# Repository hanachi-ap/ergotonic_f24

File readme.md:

# Ergotonic F24

Ergotonic F24 comes with a unique adjustable centerpiece making this keyboard split or monoblock on demand.
The Ergotonic F24 extends 30 mm horizontally and allows an adjustment of ±8 degrees with regards of the slant angle. In addition, it can also be completely separated and used as a true split.

- [About Ergotonic F24](https://hanachi-ap.github.io/ergotonic_f24/) (in Japanese)

- [How to build](https://hanachi-ap.github.io/ergotonic_f24/docs/) (in Japanese)

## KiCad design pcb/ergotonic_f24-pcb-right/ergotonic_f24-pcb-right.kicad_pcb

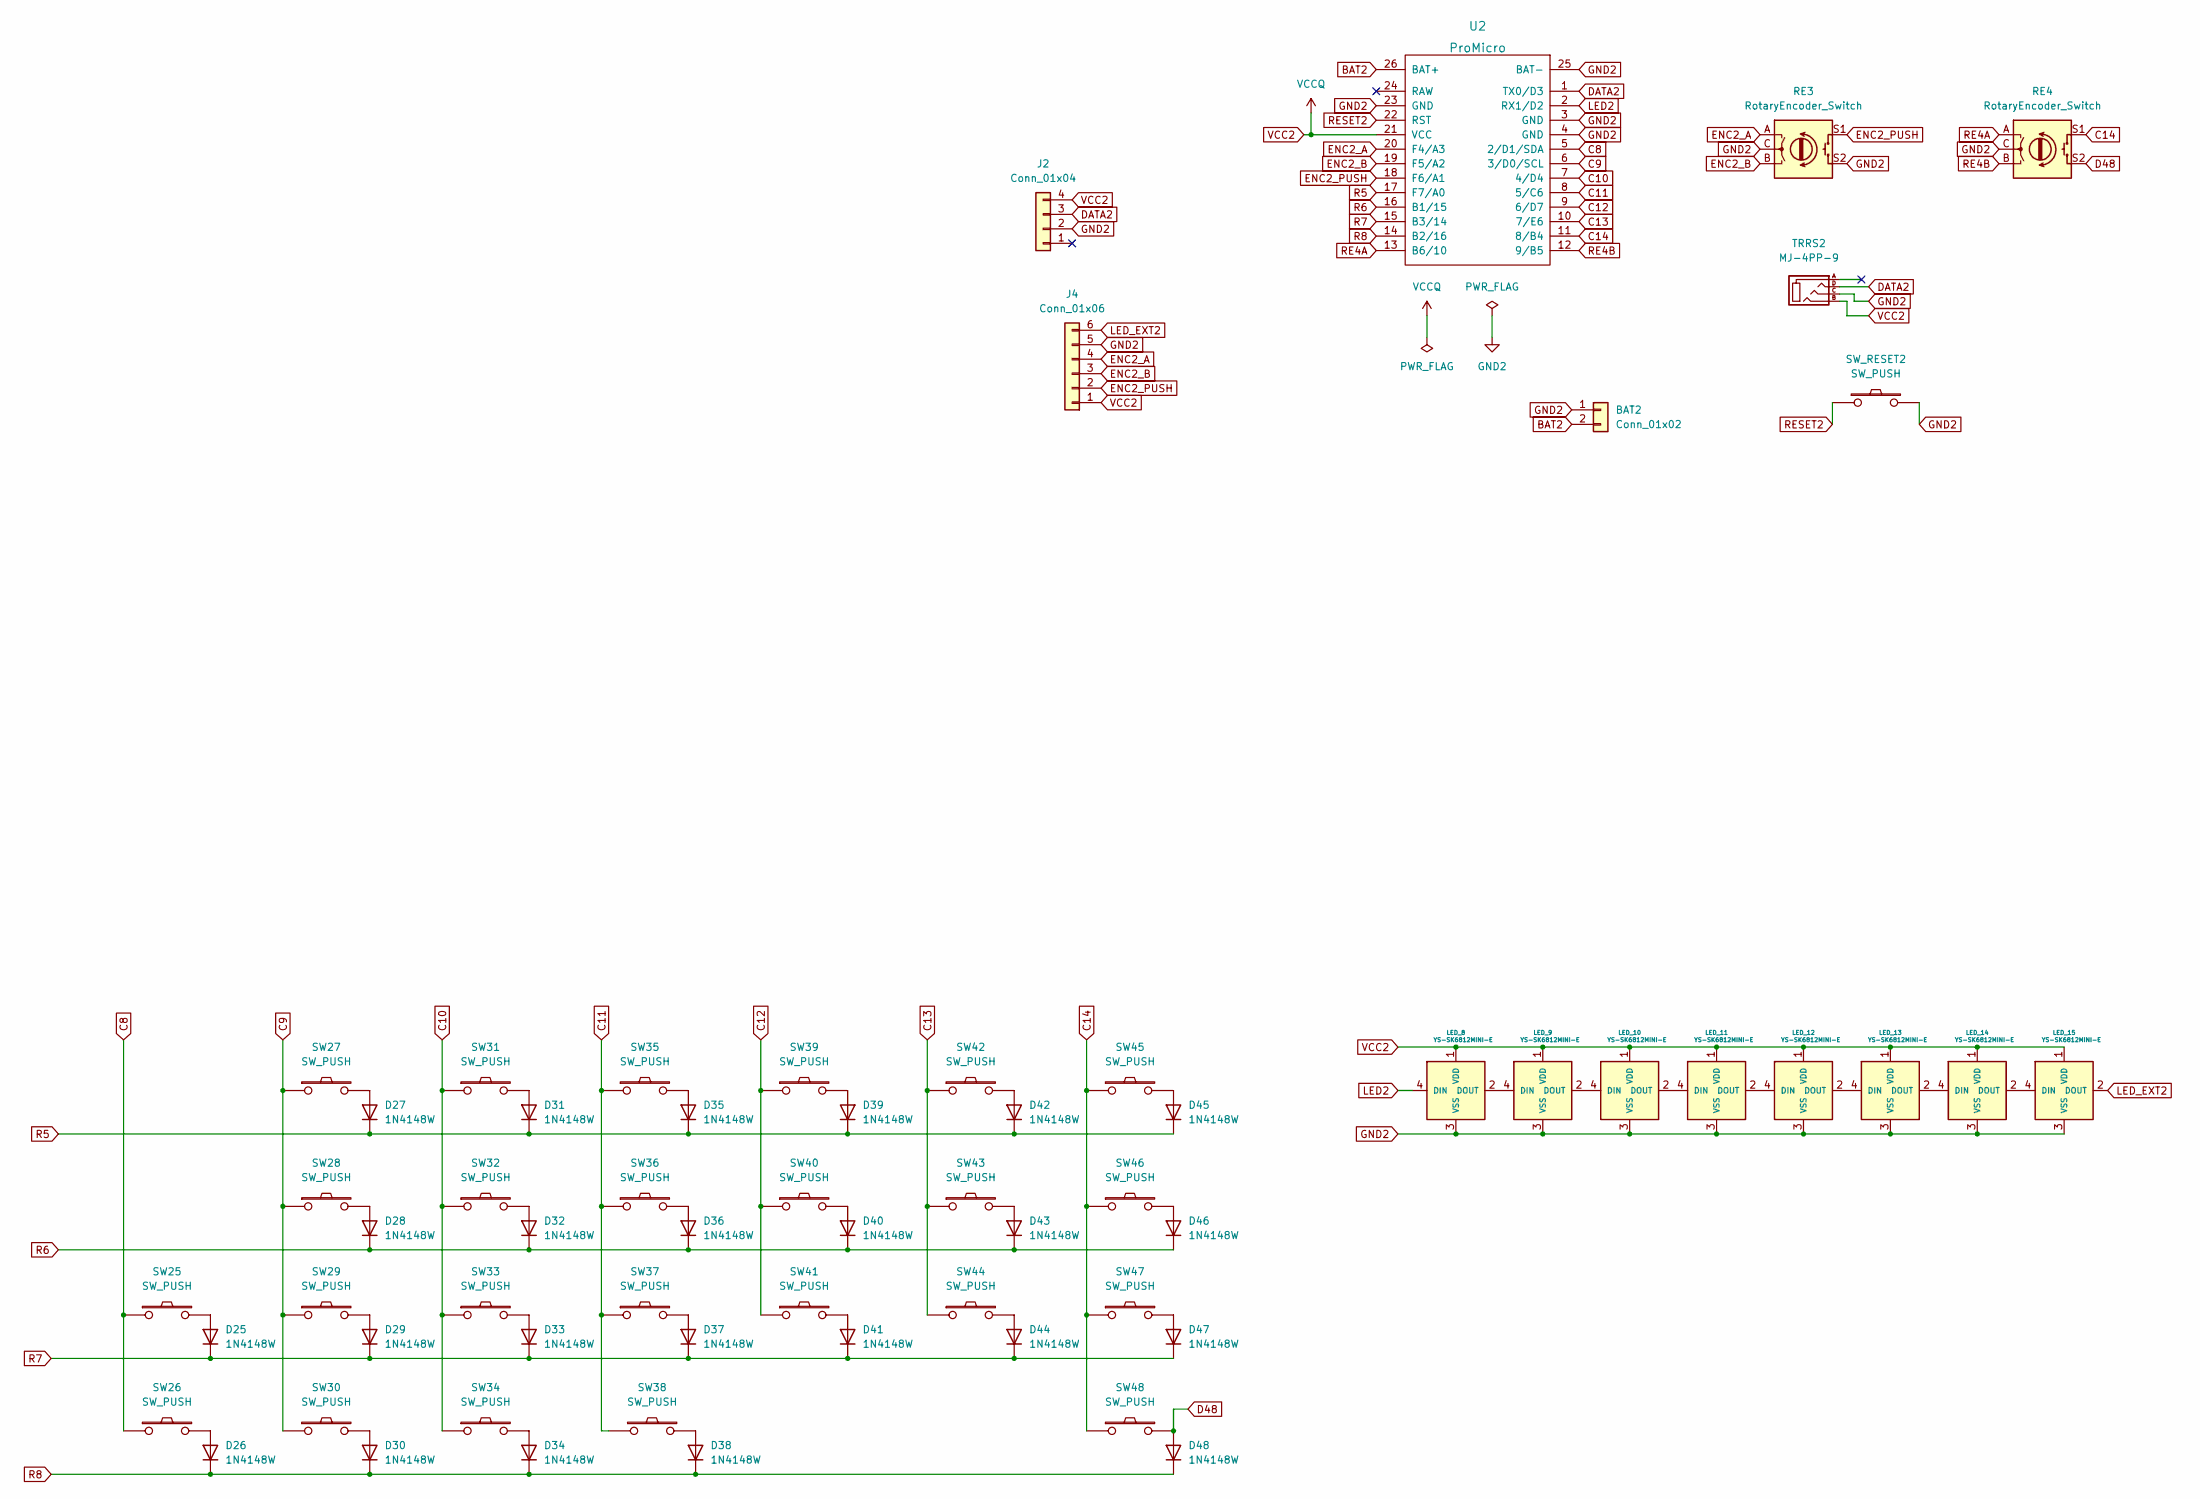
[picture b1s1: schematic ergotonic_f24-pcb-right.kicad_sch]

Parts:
BAT2: Conn_01x02; PinHeader_1x02_P2.54mm_Vertical
D25, D26, D27, D28, D29, D30, D31, D32, D33, D34, D35, D36, D37, D38, D39, D40, D41, D42, D43, D44, D45, D46, D47, D48: 1N4148W; D3_SMD_v2
J2: Conn_01x04; JST_SH_BM03B-SRSS-TB_1x04-1MP_P1.00mm_Vertical
J4: Conn_01x06; JST_SH_BM03B-SRSS-TB_1x06-1MP_P1.00mm_Vertical
LED_8, LED_9, LED_10, LED_11, LED_12, LED_13, LED_14, LED_15: YS-SK6812MINI-E
RE3, RE4: RotaryEncoder_Switch; RotaryEncoder_Alps_EC11E-Switch_Vertical_H20mm_rev2
SW25, SW26, SW27, SW28, SW29, SW30, SW31, SW32, SW33, SW34, SW35, SW36, SW37, SW38, SW39, SW40, SW41, SW42, SW43, SW44, SW45, SW46, SW47, SW48: SW_PUSH; CherryMX_Hotswap
SW_RESET2: SW_PUSH; ResetSW_1side
TRRS2: MJ-4PP-9; MJ-4PP-9_1side
U2: ProMicro

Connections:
BAT2: BAT2.2, U2.26 (BAT+)
C8: SW25.1, SW26.1, U2.5 (2/D1/SDA)
C9: SW27.1, SW28.1, SW29.1, SW30.1, U2.6 (3/D0/SCL)
C10: SW31.1, SW32.1, SW33.1, SW34.1, U2.7 (4/D4)
C11: SW35.1, SW36.1, SW37.1, SW38.1, U2.8 (5/C6)
C12: SW39.1, SW40.1, SW41.1, U2.9 (6/D7)
C13: SW42.1, SW43.1, SW44.1, U2.10 (7/E6)
C14: RE4.S1, SW45.1, SW46.1, SW47.1, SW48.1, U2.11 (8/B4)
D48: D48.2 (A), RE4.S2, SW48.2
DATA2: J2.3, TRRS2.D, U2.1 (TX0/D3)
ENC2_A: J4.4, RE3.A, U2.20 (F4/A3)
ENC2_B: J4.3, RE3.B, U2.19 (F5/A2)
ENC2_PUSH: J4.2, RE3.S1, U2.18 (F6/A1)
GND2: BAT2.1, J2.2, J4.5, LED_8.3 (VSS), LED_9.3 (VSS), LED_10.3 (VSS), LED_11.3 (VSS), LED_12.3 (VSS), LED_13.3 (VSS), LED_14.3 (VSS), LED_15.3 (VSS), RE3.C, RE3.S2, RE4.C, SW_RESET2.2, TRRS2.C, U2.3 (GND), U2.4 (GND), U2.23 (GND), U2.25 (BAT-)
LED2: LED_8.4 (DIN), U2.2 (RX1/D2)
LED_EXT2: J4.6, LED_15.2 (DOUT)
unnamed: D25.2 (A), SW25.2
unnamed: D26.2 (A), SW26.2
unnamed: D27.2 (A), SW27.2
unnamed: D28.2 (A), SW28.2
unnamed: D29.2 (A), SW29.2
unnamed: D30.2 (A), SW30.2
unnamed: D31.2 (A), SW31.2
unnamed: D32.2 (A), SW32.2
unnamed: D33.2 (A), SW33.2
unnamed: D34.2 (A), SW34.2
unnamed: D35.2 (A), SW35.2
unnamed: D36.2 (A), SW36.2
unnamed: D37.2 (A), SW37.2
unnamed: D38.2 (A), SW38.2
unnamed: D39.2 (A), SW39.2
unnamed: D40.2 (A), SW40.2
unnamed: D41.2 (A), SW41.2
unnamed: D42.2 (A), SW42.2
unnamed: D43.2 (A), SW43.2
unnamed: D44.2 (A), SW44.2
unnamed: D45.2 (A), SW45.2
unnamed: D46.2 (A), SW46.2
unnamed: D47.2 (A), SW47.2
unnamed: LED_8.2 (DOUT), LED_9.4 (DIN)
unnamed: LED_10.2 (DOUT), LED_11.4 (DIN)
unnamed: LED_9.2 (DOUT), LED_10.4 (DIN)
unnamed: LED_11.2 (DOUT), LED_12.4 (DIN)
unnamed: LED_12.2 (DOUT), LED_13.4 (DIN)
unnamed: LED_13.2 (DOUT), LED_14.4 (DIN)
unnamed: LED_14.2 (DOUT), LED_15.4 (DIN)
R5: D27.1 (K), D31.1 (K), D35.1 (K), D39.1 (K), D42.1 (K), D45.1 (K), U2.17 (F7/A0)
R6: D28.1 (K), D32.1 (K), D36.1 (K), D40.1 (K), D43.1 (K), D46.1 (K), U2.16 (B1/15)
R7: D25.1 (K), D29.1 (K), D33.1 (K), D37.1 (K), D41.1 (K), D44.1 (K), D47.1 (K), U2.15 (B3/14)
R8: D26.1 (K), D30.1 (K), D34.1 (K), D38.1 (K), D48.1 (K), U2.14 (B2/16)
RE4A: RE4.A, U2.13 (B6/10)
RE4B: RE4.B, U2.12 (9/B5)
RESET2: SW_RESET2.1, U2.22 (RST)
VCC2: J2.4, J4.1, LED_8.1 (VDD), LED_9.1 (VDD), LED_10.1 (VDD), LED_11.1 (VDD), LED_12.1 (VDD), LED_13.1 (VDD), LED_14.1 (VDD), LED_15.1 (VDD), TRRS2.B, U2.21 (VCC)

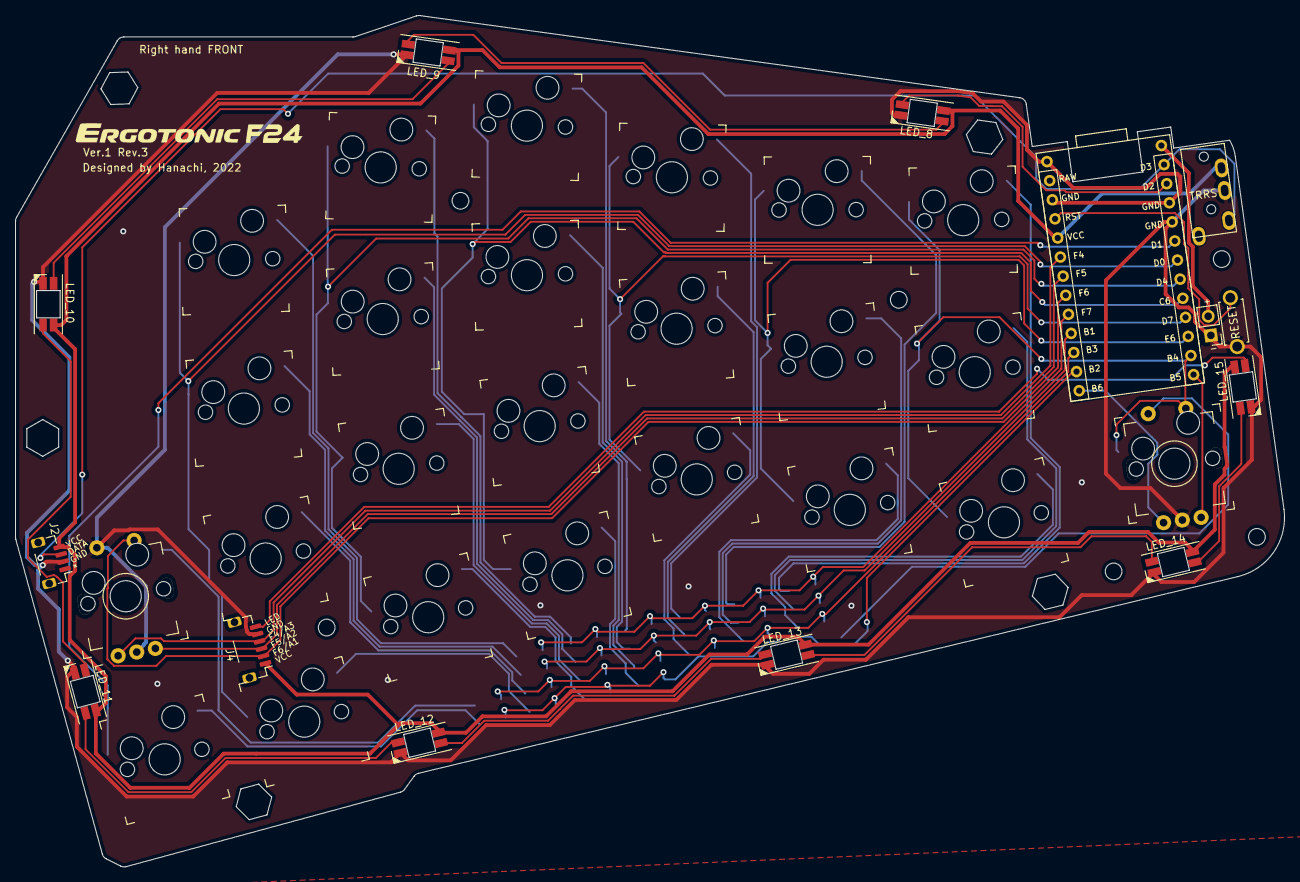
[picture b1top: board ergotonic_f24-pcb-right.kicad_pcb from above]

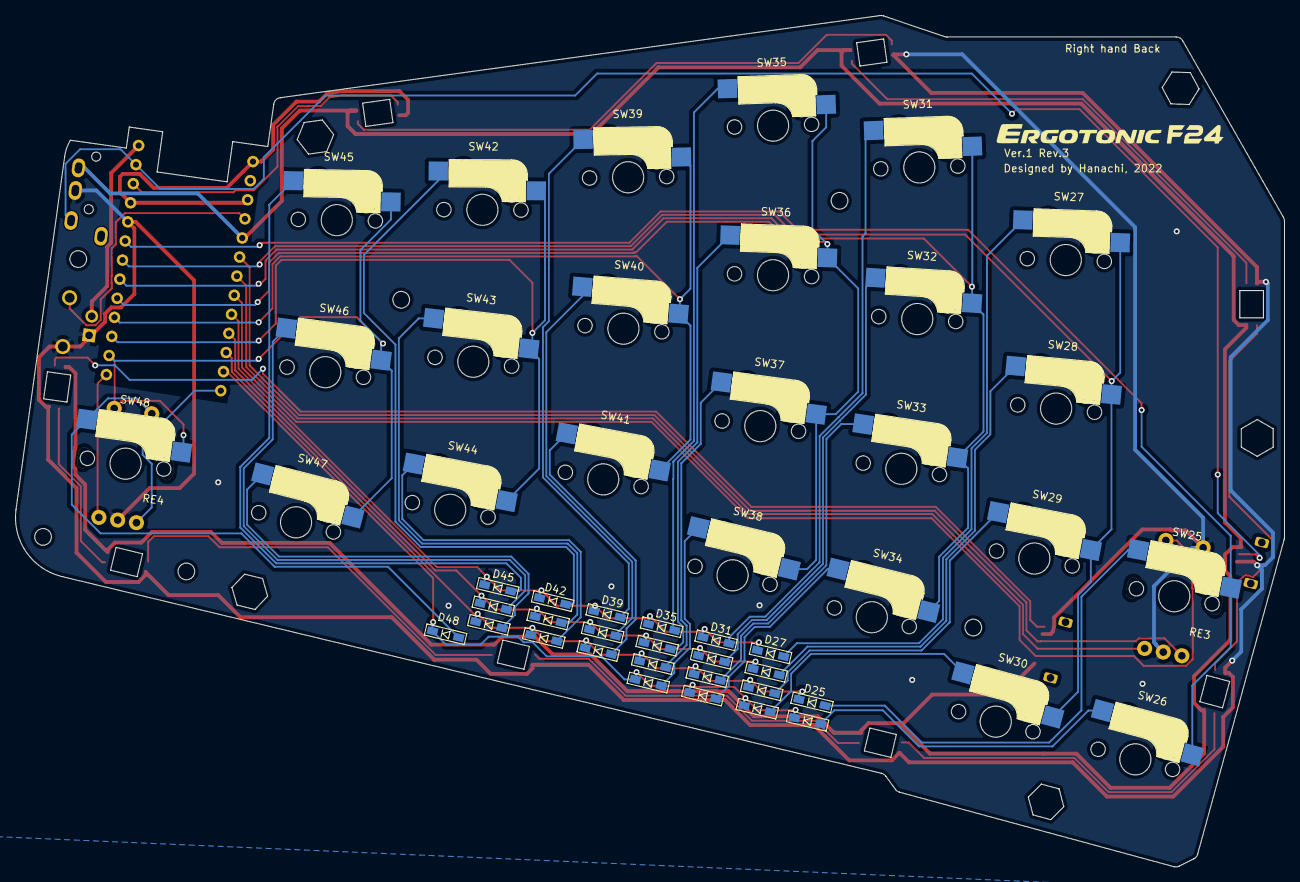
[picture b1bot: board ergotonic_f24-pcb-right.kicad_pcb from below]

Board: 2 copper layers, 167.2 x 112.2 mm, 64 parts (24 on the bottom side), 54 nets.

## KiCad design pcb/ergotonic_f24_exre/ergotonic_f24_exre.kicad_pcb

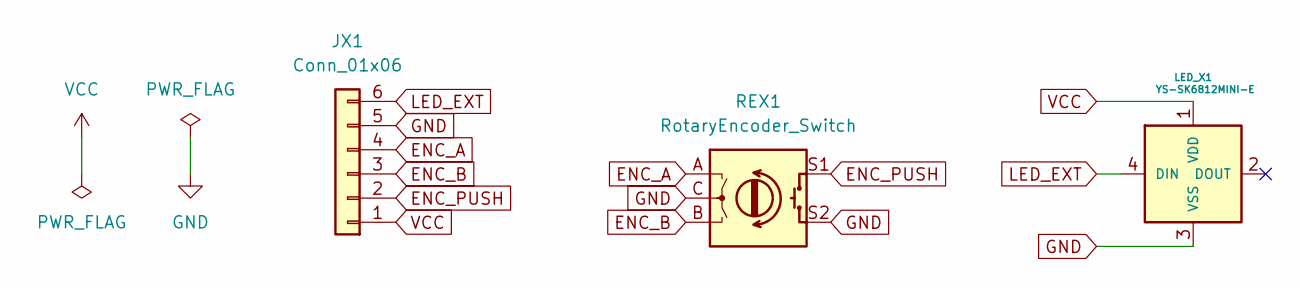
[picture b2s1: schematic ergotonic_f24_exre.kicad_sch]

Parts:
JX1: Conn_01x06; JST_SH_BM03B-SRSS-TB_1x06-1MP_P1.00mm_Vertical
LED_X1: YS-SK6812MINI-E
REX1: RotaryEncoder_Switch; RotaryEncoder_Alps_EC11E-Switch_Vertical_H20mm_rev2

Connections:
ENC_A: JX1.4, REX1.A
ENC_B: JX1.3, REX1.B
ENC_PUSH: JX1.2, REX1.S1
GND: JX1.5, LED_X1.3 (VSS), REX1.C, REX1.S2
LED_EXT: JX1.6, LED_X1.4 (DIN)
VCC: JX1.1, LED_X1.1 (VDD)

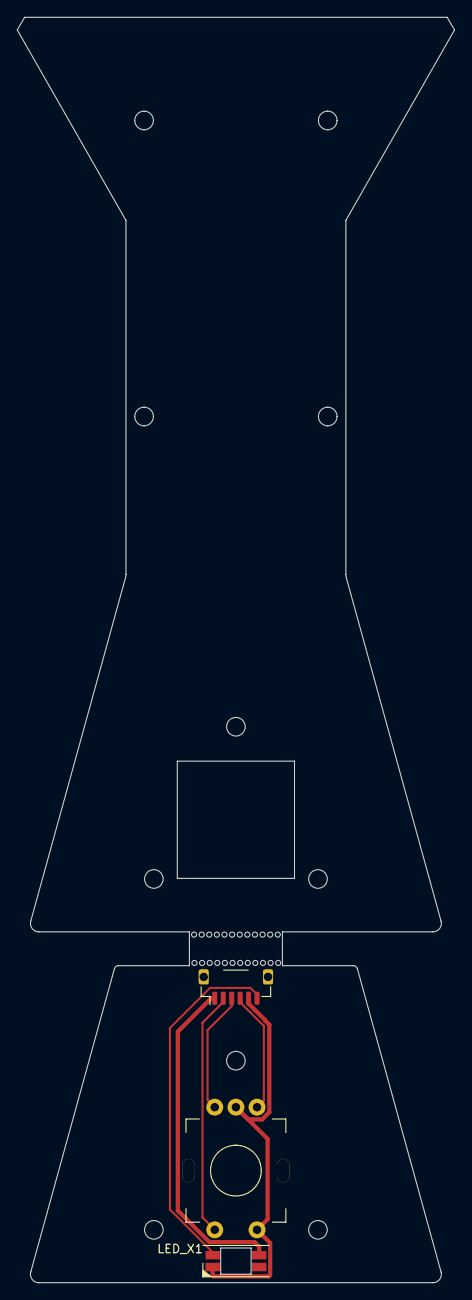
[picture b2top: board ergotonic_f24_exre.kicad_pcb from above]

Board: 2 copper layers, 51.7 x 149.6 mm, 3 parts (0 on the bottom side), 6 nets.

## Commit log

2022-03-11 initial
2022-03-12 change: readme.md
2022-03-17 modify: buildguide
2022-03-21 modified firmware (added encoder feature)
2022-03-21 add hex file
2022-03-21 fix: encoder control
2022-03-27 modify: index.md
2022-04-01 fix; encoder support in VIA
2022-04-01 update: firmware binary (support encoder in VIA)
2022-04-01 update: documents
2022-07-23 ver1 rev2 base
2022-07-24 v1r2: Preparing for publication
2022-07-24 modify: index.md, add: ergotonic_f49_layout_desigen
2022-07-24 Set theme jekyll-theme-slate
2022-07-24 Set theme jekyll-theme-hacker
2022-07-24 update: buildguide
2022-07-24 Set theme jekyll-theme-tactile
2022-07-25 Update: guildguide
2022-08-20 Version 1 Revision 3
2022-08-20 modify: firmware
2022-08-21 Set theme jekyll-theme-midnight
2022-08-22 Fix: firmware minor issues
2022-08-22 fix: documednt bug
2022-08-22 fix documednts
2022-08-22 fix document typo
2022-09-03 gerber data is no longer publicly available
2022-09-04 add: acrylic data
2022-09-04 add: acrylic data(zip)
2022-09-04 add: acrylic data(png)
2022-09-04 Fix wrong color
2022-09-08 Improve deprecated definition
2022-09-09 add note
2022-09-15 add: aki27kbd keymap (for truckball module)
2022-09-17 add keymap for cocot TrackBall module
2022-09-17 improve buildguide
2022-09-18 update: acrylic cut data
2022-09-18 update aclylic cut data
2022-09-22 fix aclylic cut data
2022-09-22 fix aclylic cut data (add zip file)
2022-09-24 add ble_micro_pro/
2024-07-30 Added STL files for variable wing mechanism
2024-08-10 Firmware update. Transferred source code to a separate repository.
2024-08-16 add stl files
2024-08-16 Add profile file for ble micro
